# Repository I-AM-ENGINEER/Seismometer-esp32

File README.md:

#Work in progress

# Seismometer-esp32
ESP32 based wifi vibration &amp; sound sensor with realtime streaming captured audio throught mqtt

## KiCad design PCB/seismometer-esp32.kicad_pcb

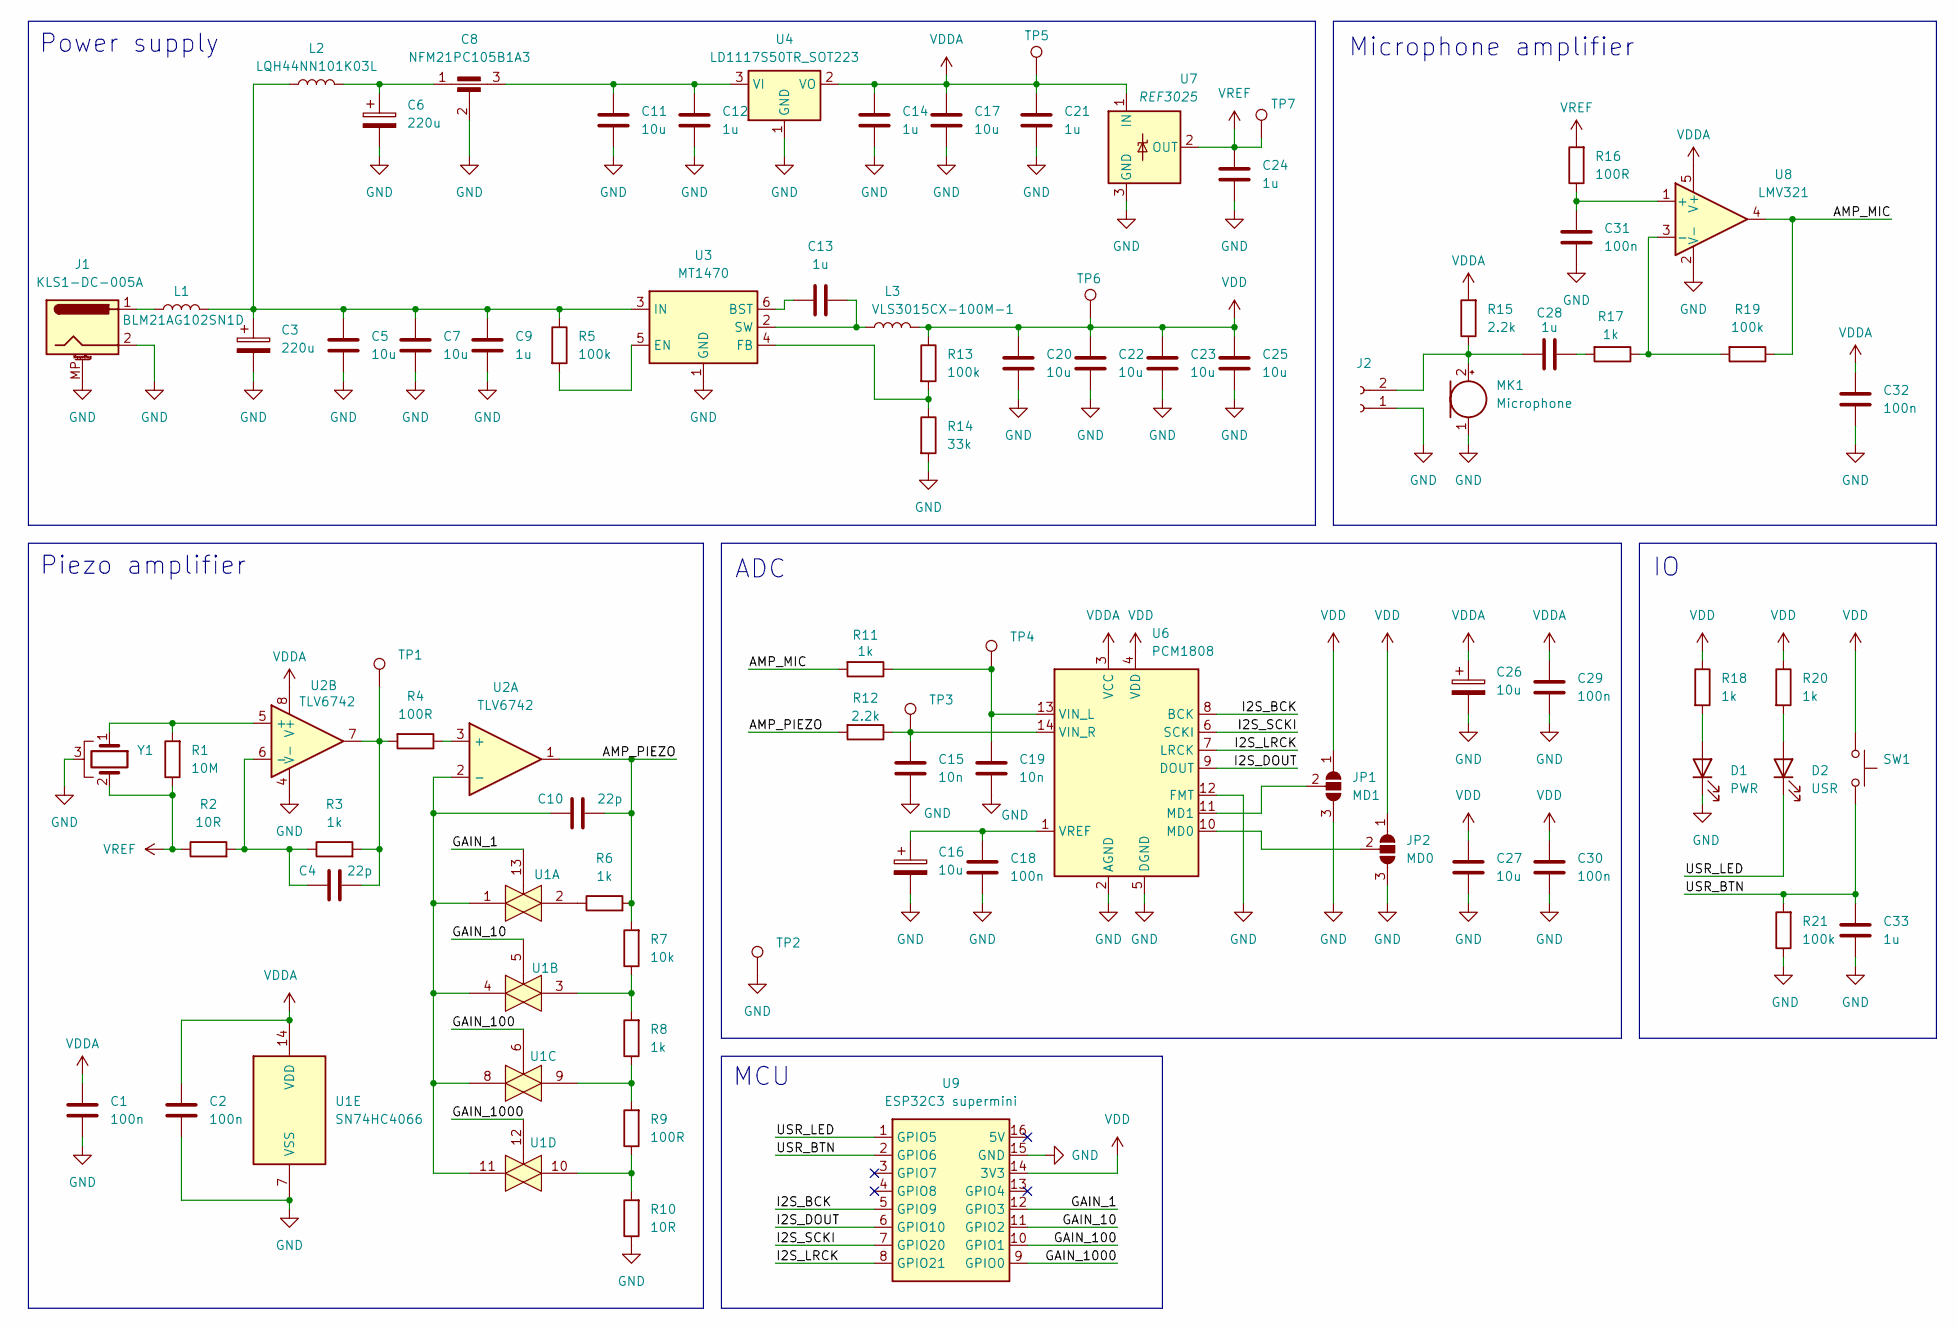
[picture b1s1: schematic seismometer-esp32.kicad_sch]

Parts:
C1, C2, C18, C29, C30, C31, C32: 100n; C_0603_1608Metric_Pad1.08x0.95mm_HandSolder
C3, C6: 220u; CP_Elec_6.3x7.7
C4, C10: 22p; C_0603_1608Metric_Pad1.08x0.95mm_HandSolder
C5, C7, C11, C17, C20, C22, C23, C25, C27: 10u; C_0603_1608Metric_Pad1.08x0.95mm_HandSolder
C8: NFM21PC105B1A3; NFM21PC
C9, C12, C13, C14, C21, C24, C28, C33: 1u; C_0603_1608Metric_Pad1.08x0.95mm_HandSolder
C15, C19: 10n; C_0603_1608Metric_Pad1.08x0.95mm_HandSolder
C16, C26: 10u; CP_EIA-3216-12_Kemet-S_Pad1.58x1.35mm_HandSolder
D1: PWR; LED_D5.0mm
D2: USR; LED_D5.0mm
J1: KLS1-DC-005A; BarrelJack_Kycon_KLDX-0202-xC_Horizontal
J2: Conn_01x02_Socket; PinHeader_1x02_P2.00mm_Vertical
JP1: MD1; SolderJumper-3_P1.3mm_Open_RoundedPad1.0x1.5mm
JP2: MD0; SolderJumper-3_P1.3mm_Open_RoundedPad1.0x1.5mm
L1: BLM21AG102SN1D; C_0805_2012Metric
L2: LQH44NN101K03L; L_Taiyo-Yuden_NR-40xx_HandSoldering
L3: VLS3015CX-100M-1; L_Taiyo-Yuden_NR-30xx_HandSoldering
MK1: Microphone; DGO9465CD
R1: 10M; R_0603_1608Metric_Pad0.98x0.95mm_HandSolder
R2, R10: 10R; R_0603_1608Metric_Pad0.98x0.95mm_HandSolder
R3, R6, R8, R11, R17, R18, R20: 1k; R_0603_1608Metric_Pad0.98x0.95mm_HandSolder
R4, R9, R16: 100R; R_0603_1608Metric_Pad0.98x0.95mm_HandSolder
R5, R13, R19, R21: 100k; R_0603_1608Metric_Pad0.98x0.95mm_HandSolder
R7: 10k; R_0603_1608Metric_Pad0.98x0.95mm_HandSolder
R12, R15: 2.2k; R_0603_1608Metric_Pad0.98x0.95mm_HandSolder
R14: 33k; R_0603_1608Metric_Pad0.98x0.95mm_HandSolder
SW1: SW_Push; SW_Push_1P1T_NO_6x6mm_H9.5mm
TP1, TP2, TP3, TP4, TP5, TP6, TP7: TestPoint; TestPoint_Pad_D2.0mm
U1: SN74HC4066; SO-14_3.9x8.65mm_P1.27mm
U2: TLV6742; SSOP-8_3.9x5.05mm_P1.27mm
U3: MT1470; TSOT-23-6
U4: LD1117S50TR_SOT223; SOT-223-3_TabPin2
U6: PCM1808; SSOP-14_5.3x6.2mm_P0.65mm
U7: REF3025; SOT-23
U8: LMV321; SOT-23-5
U9: ESP32C3 supermini; ESP32C3-supermini
Y1: Crystal_GND3; Shielded cable 2pin

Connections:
/AMP_MIC: R11.2, R19.1, U8.4
/AMP_PIEZO: C10.2, R6.2, R7.2, R12.2, U2.1
/GAIN_1: U1.13, U9.12 (GPIO3)
/GAIN_10: U1.5, U9.11 (GPIO2)
/GAIN_100: U1.6, U9.10 (GPIO1)
/GAIN_1000: U1.12, U9.9 (GPIO0)
/I2S_BCK: U6.8 (BCK), U9.5 (GPIO9)
/I2S_DOUT: U6.9 (DOUT), U9.6 (GPIO10)
/I2S_LRCK: U6.7 (LRCK), U9.8 (GPIO21)
/I2S_SCKI: U6.6 (SCKI), U9.7 (GPIO20)
/USR_BTN: C33.1, R21.2, SW1.2, U9.2 (GPIO6)
/USR_LED: D2.1 (K), U9.1 (GPIO5)
GND: C1.2, C2.2, C3.2, C5.2, C6.2, C7.2, C8.2, C9.2, C11.2, C12.2, C14.2, C15.2, C16.2, C17.2, C18.2, C19.2, C20.2, C21.2, C22.2, C23.2, C24.2, C25.2, C26.2, C27.2, C29.2, C30.2, C31.1, C32.2, C33.2, D1.1 (K), J1.2, J1.MP (MountPin), J2.1, JP1.3 (B), JP2.3 (B), MK1.1 (-), R10.1, R14.2, R21.1, TP2.1, U1.7 (VSS), U2.4 (V-), U3.1 (GND), U4.1 (GND), U6.2 (AGND), U6.5 (DGND), U6.12 (FMT), U7.3 (GND), U8.2 (V-), U9.15 (GND), Y1.3
unnamed: C4.2, R3.2, R4.2, TP1.1, U2.7
unnamed: C6.1, C8.1, L2.2
unnamed: C28.2, R17.2
unnamed: D1.2 (A), R18.2
unnamed: D2.2 (A), R20.2
unnamed: J1.1, L1.1
unnamed: C28.1, J2.2, MK1.2 (+), R15.1
unnamed: JP1.2 (C), U6.11 (MD1)
unnamed: JP2.2 (C), U6.10 (MD0)
unnamed: R6.1, U1.2
unnamed: R7.1, R8.2, U1.3
unnamed: R8.1, R9.2, U1.9
unnamed: R9.1, R10.2, U1.10
unnamed: R4.1, U2.3 (+)
unnamed: C10.1, U1.1, U1.4, U1.8, U1.11, U2.2 (-)
unnamed: R1.2, U2.5 (+), Y1.1
unnamed: C4.1, R2.2, R3.1, U2.6 (-)
unnamed: C13.1, U3.6 (BST)
unnamed: R5.2, U3.5 (EN)
unnamed: R13.2, R14.1, U3.4 (FB)
unnamed: C3.1, C5.1, C7.1, C9.1, L1.2, L2.1, R5.1, U3.3 (IN)
unnamed: C13.2, L3.1, U3.2 (SW)
unnamed: C8.3, C11.1, C12.1, U4.3 (VI)
unnamed: C19.1, R11.1, TP4.1, U6.13 (VIN_L)
unnamed: C15.1, R12.1, TP3.1, U6.14 (VIN_R)
unnamed: C16.1, C18.1, U6.1 (VREF)
unnamed: C31.2, R16.1, U8.1 (+)
unnamed: R17.1, R19.2, U8.3 (-)
VDD: C20.1, C22.1, C23.1, C25.1, C27.1, C30.1, JP1.1 (A), JP2.1 (A), L3.2, R13.1, R18.1, R20.1, SW1.1, TP6.1, U6.4 (VDD), U9.14 (3V3)
VDDA: C1.1, C2.1, C14.1, C17.1, C21.1, C26.1, C29.1, C32.1, R15.2, TP5.1, U1.14 (VDD), U2.8 (V+), U4.2 (VO), U6.3 (VCC), U7.1 (IN), U8.5 (V+)
VREF: C24.1, R1.1, R2.1, R16.2, TP7.1, U7.2 (OUT), Y1.2

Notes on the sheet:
ADC
Power supply
Piezo amplifier
Microphone amplifier
MCU

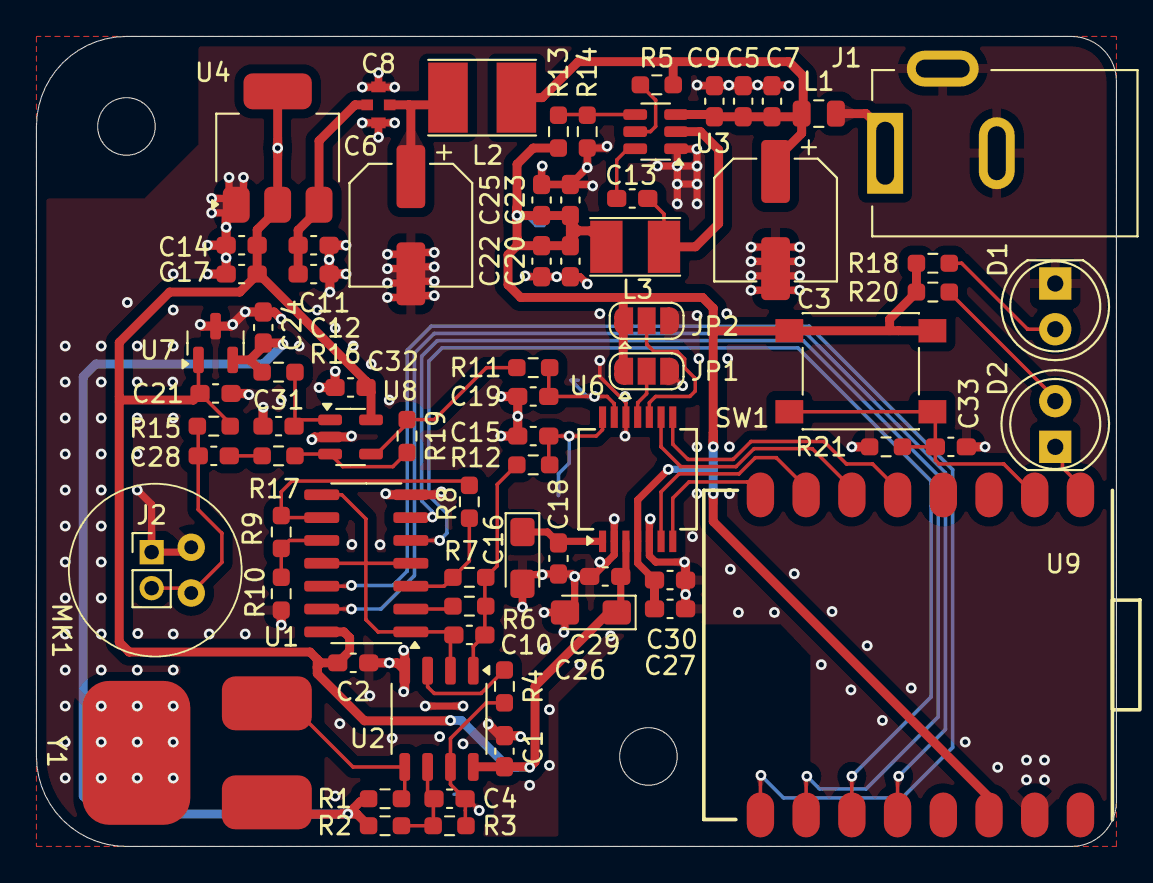
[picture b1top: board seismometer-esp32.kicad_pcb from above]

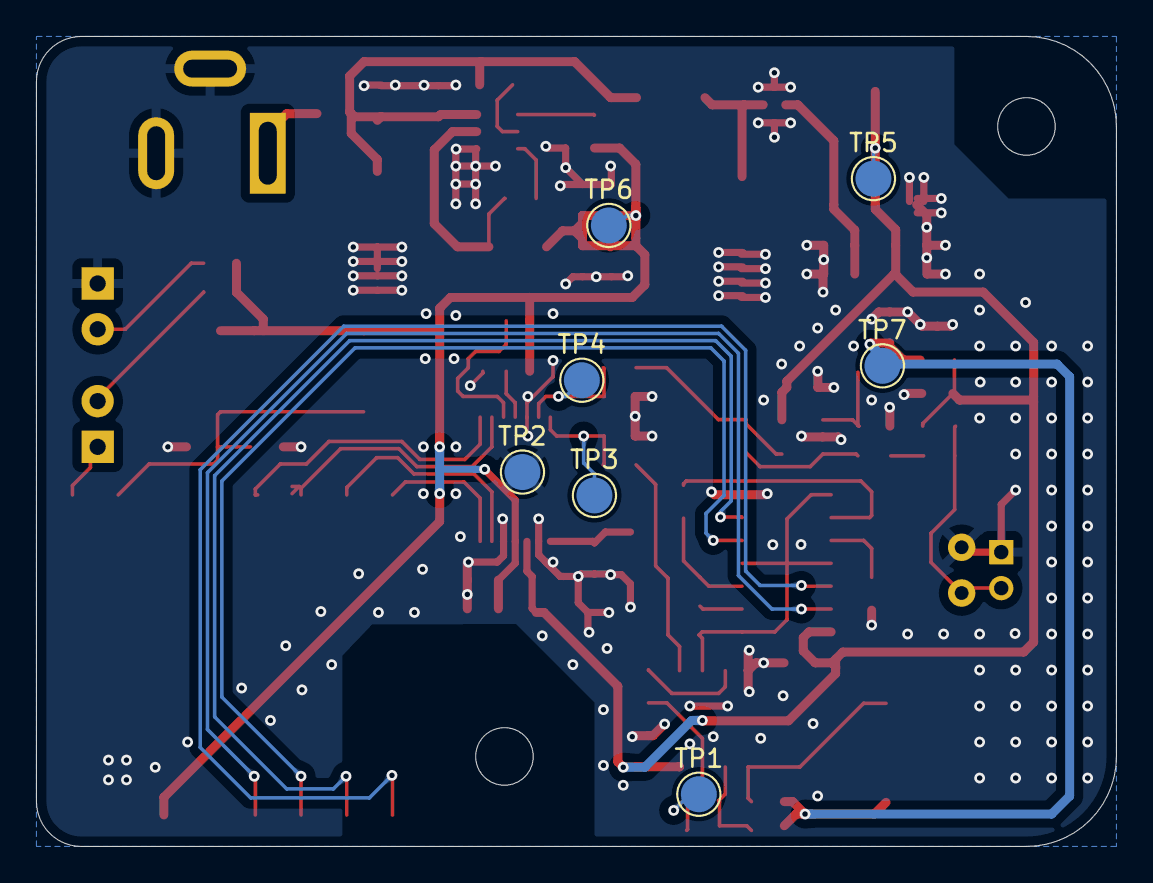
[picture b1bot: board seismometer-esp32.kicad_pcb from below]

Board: 2 copper layers, 60.0 x 45.0 mm, 81 parts (7 on the bottom side), 44 nets.

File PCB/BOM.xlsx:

Reference | Value | Qty
C1,C2,C18,C29,C30,C31,C32 | 100n | 7
C3,C6 | 220u | 2
C4,C10 | 22p | 2
C5,C7,C11,C16,C17,C20,C22,C23,C25,C26,C27 | 10u | 11
C8 | NFM21PC105B1A3 | 1
C9,C12,C13,C14,C21,C24,C28,C33 | 1u | 8
C15,C19 | 10n | 2
J1 | KLS1-DC-005A | 1
L1 | BLM21AG102SN1D | 1
L2 | LQH44NN101K03L | 1
L3 | VLS3015CX-100M-1 | 1
MK1 | Microphone | 1
R1 | 10M | 1
R2,R10 | 10R | 2
R3,R6,R8,R11,R17,R18,R20 | 1k | 7
R4,R9,R16 | 100R | 3
R5,R13,R19,R21 | 100k | 4
R7 | 10k | 1
R12,R15 | 2.2k | 2
R14 | 33k | 1
U1 | SN74HC4066 | 1
U2 | TLV6742 | 1
U3 | MT1470 | 1
U4 | LD1117S50TR_SOT223 | 1
U6 | PCM1808 | 1
U7 | REF3025 | 1

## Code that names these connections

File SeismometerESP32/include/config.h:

#ifndef CONFIG_H__
#define CONFIG_H__

#define I2S_RAW_QUEUE_LENGTH                2
//#define UDP_PACKAGE_LENGTH                  3840
//#define UDP_PACKAGE_QUEUE_LENGTH            1

#define WIFI_TSF_SAMPLE_PERIOD_MS           (5000)
#define WIFI_TSF_SAMPLERATE                 (50)
#define TCP_PACKAGE_LENGTH                  1460
#define TCP_PACKAGE_QUEUE_LENGTH            1
#define TCP_RECONNECT_DELAY_MS              100
#define TCP_MAX_RETRY_DELAY_MS              60000
// Valid: 96000, 64000, 48000, 32000, 16000, 8000
#define I2S_SAMPLERATE                      32000

// Multiply to 4*2 for get bytes size
#define I2S_DMA_FRAMES                      120
#define I2S_DMA_FRAME_SIZE                  8
#define I2S_SAMPLES_MONO_FRAME              (I2S_DMA_FRAMES * I2S_DMA_FRAME_SIZE / 2 / 3)
#define I2S_SAMPLES_STEREO_FRAME            (I2S_SAMPLES_MONO_FRAME * 2)
#define I2S_DMA_FRAMES_BUFFER               4

#define IP_TARGET                           "192.168.1.17"
#define IP_TARGET_PORT                      1883
#define MQTT_USERNAME                       "demo"
#define MQTT_PASSWORD                       "demo"

#define GPIO_BTN_PIN                        GPIO_NUM_6
#define GPIO_LED_PIN                        GPIO_NUM_5

#define WIFI_SSID                           "5G_COVID_BASE_STATION"
#define WIFI_PWD                            "1SimplePass9"

#define GPIO_GAIN_1_PIN                     GPIO_NUM_3
#define GPIO_GAIN_10_PIN                    GPIO_NUM_2
#define GPIO_GAIN_100_PIN                   GPIO_NUM_1
#define GPIO_GAIN_1000_PIN                  GPIO_NUM_0

#define TFS_SYNC_TIME_PERIOD_S      (5)
#define TFS_SYNC_TFS_PERIOD_MS      (100)
#define TFS_SYNC_ARRAY_COUNT        ((1000/TFS_SYNC_TFS_PERIOD_MS)*TFS_SYNC_TIME_PERIOD_S)
#define TFS_EXPECTED_GAIN           (40)




#define I2S_DMA_BUFFER_SIZE                 I2S_DMA_FRAMES * I2S_DMA_FRAME_SIZE

#endif // !CONFIG_H__

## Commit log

2024-09-17 PCB upload
2024-10-25 3d models & case
2025-02-01 Before changes I2S driver
2025-02-02 Gain finding work
2025-02-07 BLAME ALL REWRITE ALL
2025-02-10 Circular buffer realization
2025-02-10 Accuracy time
2025-02-10 I2S reader
2025-02-12 MQTT + simple DSP
2025-02-13 Almost work, but i2s jitter
2025-02-18 MQTT sending work
2025-02-18 Better timestamp with Theil–Sen
2025-02-19 TSF mesh vs TSF wifi compare
2025-02-19 Rename folder
2025-02-19 TSF_AP
2025-02-22 Cleanup
2025-02-26 Temp backup
